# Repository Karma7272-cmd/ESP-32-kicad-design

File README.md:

#  Electronics PCB Designs

A collection of my **electronics circuits, PCB designs, and hardware projects** in a single repository.

##  Projects

This repository contains:

* PCB Designs
* Circuit Schematics
* Power Electronics
* Microcontroller Boards
* Sensor Circuits
* Motor Control Circuits
* IoT Projects
* Other Electronics Projects

##  Tools

* KiCad
* EasyEDA
* Altium Designer
* LTspice
* MATLAB/Simulink

##  Structure

```text
Electronics-PCB-Designs/
│
├── Project-01/
├── Project-02/
├── Project-03/
├── Project-04/
├── Project-05/
└── README.md
```

project may contain:

```text
├── Schematic/
├── PCB/
├── Gerber/
├── BOM/
└── Images/
```

##  Purpose

This repository is used to **store, organize, and share my electronics and PCB designs**.

##  Status

Continuously adding new designs and projects.

---

**Made for learning, prototyping, and electronics development.**

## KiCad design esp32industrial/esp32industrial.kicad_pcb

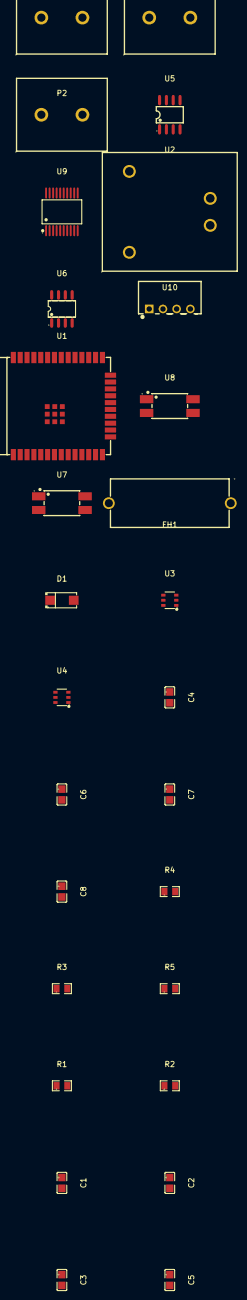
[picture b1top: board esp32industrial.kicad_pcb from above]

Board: 2 copper layers, 28 parts (0 on the bottom side), 26 nets, no tracks yet.

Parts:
C1, C4, C5, C6, C7, C8: 100nF; C0805
C2, C3: 10uF; C0805
D1: SMAJ24A-C148222; SMA_L4.4-W2.6-LS5.0-RD
FH1: PTF-15; FUSE-TH_L22.0-W9.0-P22.60
P1, P2, P3: WJ25C-B-2P; CONN-TH_2P-P7.62_WJ25C-B-7.62-2P
R1, R2, R5: 10k; R0805
R3: 470R; R0805
R4: 1k; R0805
U1: ESP32-WROOM-32E; WIFI-SMD_ESP32-WROOM-32E
U2: VB02-T2S05; PWRM-TH_VB02-T2SXX
U3, U4: LT8306RS6#TRMPBF; TSOT-23-6_L2.9-W1.6-P0.95-LS2.8-BR
U5: MAX485ESA+T; SOIC-8_L5.0-W4.0-P1.27-LS6.0-BL
U6: ADUM1201ARZ-RL7; SOIC-8_L4.9-W3.9-P1.27-LS6.0-BL
U7, U8: PC817X3CSP9F; OPTO-SMD-4_L4.6-W6.5-P2.54-LS10.3-TL
U9: ADE7753ARSZRL; SSOP-20_L7.2-W5.3-P0.65-LS7.8-BL
U10: B0505S-1W; PWRM-TH_BXXXXS-1W

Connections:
+3.3V: C1.1, C5.1, R1.1, R2.2, R5.1, U1.2, U6.1
AC_L: FH1.2, U2.1
AC_N: P1.2, U2.2
GND: C1.2, C2.2, C3.2, C4.2, C5.2, C6.2, C7.2, C8.2, U1.1, U1.15, U1.38, U1.39, U2.4, U3.2, U4.2, U5.5, U6.4, U6.5, U7.2, U8.3, U9.5, U9.6, U9.8, U9.10, U10.1, U10.3
ISO_5V: C4.1, C6.1, C7.1, C8.1, U2.3, U5.8, U6.8, U9.2, U9.3, U10.2, U10.4
ISO_OUT_N: P3.2, R4.2, U7.3
ISO_OUT_P: P3.1, U7.4, U8.2
MCU_RX: U1.34, U6.2
MCU_TX: U1.35, U6.7
N_2967D35D: R1.2, U1.3
N_40660994: R3.2, U1.11
N_49157677: FH1.1, P1.1
N_DBA963B1: R2.1, U1.25
OPT_IN_MCU: R5.2, U1.12, U8.4
RS485_A: D1.1, P2.1, U5.6
RS485_B: D1.2, P2.2, U5.7
RS485_DE_RE: U1.26, U5.2, U5.3
RS485_RX: U5.1, U6.3
RS485_TX: U5.4, U6.6
SERIES_R3_N_1_U7_N_1: R3.1, U7.1
SERIES_R4_N_1_U8_N_1: R4.1, U8.1
SPI_CLK: U1.30, U9.18
SPI_CS: U1.29, U9.17
SPI_MISO: U1.31, U9.19
SPI_MOSI: U1.37, U9.20
VIN: C2.1, C3.1, U3.5, U4.5
